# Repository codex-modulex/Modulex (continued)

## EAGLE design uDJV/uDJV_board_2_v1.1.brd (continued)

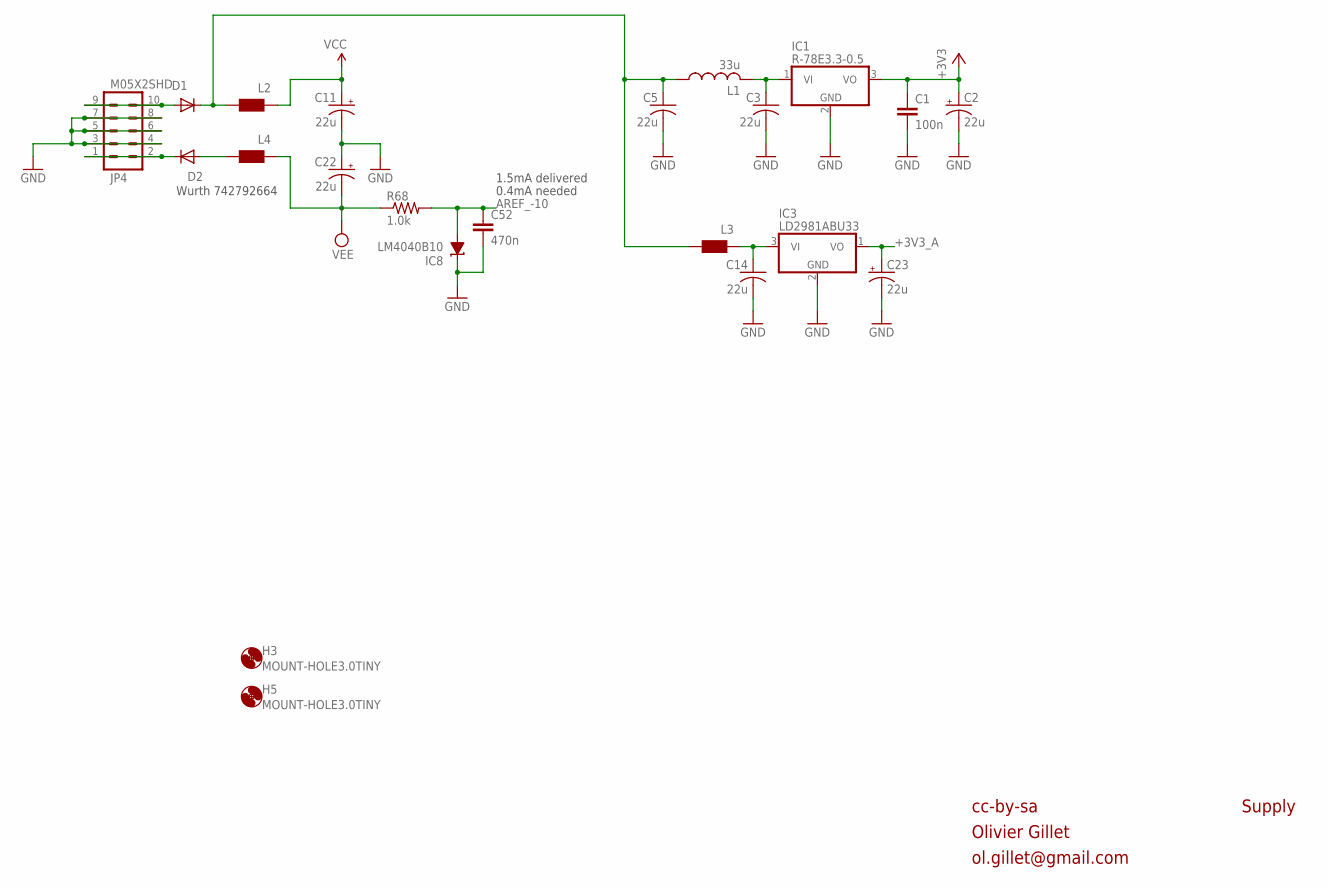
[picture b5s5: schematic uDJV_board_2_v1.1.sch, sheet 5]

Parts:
C1: 100n; PARTS_AMAN_RESISTOR_0603
C2, C11, C22, C23: 22u; PANASONIC_C
C3, C5, C14: 22u; C1206
C52: 470n; PARTS_AMAN_RESISTOR_0603
D1, D2: 1N5819HW; SOD123
H3, H5: MOUNT-HOLE3.0TINY; 3,0TINY
IC1: R-78E3.3-0.5; WE78
IC3: LD2981ABU33; SOT89
IC8: LM4040B10; DBZ_R-PDSO-G3
JP4: M05X2SHD; 2X5-SHROUDED
L1: 33u; L2012C
L2, L3, L4: WE-CBF_0603; 0603
R68: 1.0k; PARTS_AMAN_RESISTOR_0603

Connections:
+3V3: C1.1, C2.+, IC1.3 (VO); also elsewhere on the board
+3V3_A: C23.+, IC3.1 (VO); also elsewhere on the board
AREF_-10: C52.1, IC8.2 (A), R68.2; also elsewhere on the board
GND: C1.2, C2.-, C3.2, C5.2, C11.-, C14.2, C22.+, C23.-, C52.2, IC1.2 (GND), IC3.2 (GND), IC8.1 (C), JP4.3, JP4.4, JP4.5, JP4.6, JP4.7, JP4.8; also elsewhere on the board
unnamed: C14.1, IC3.3 (VI), L3.1
unnamed: C5.1, D1.C, L1.1, L2.2, L3.2
unnamed: D2.A, L4.2
unnamed: C3.1, IC1.1 (VI), L1.2
unnamed: D1.A, JP4.9, JP4.10
unnamed: D2.C, JP4.1, JP4.2
VCC: C11.+, L2.1; also elsewhere on the board
VEE: C22.-, L4.1, R68.1; also elsewhere on the board

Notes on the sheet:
0.4mA needed
cc-by-sa
Olivier Gillet
ol.gillet@gmail.com
Supply
Wurth 742792664
1.5mA delivered

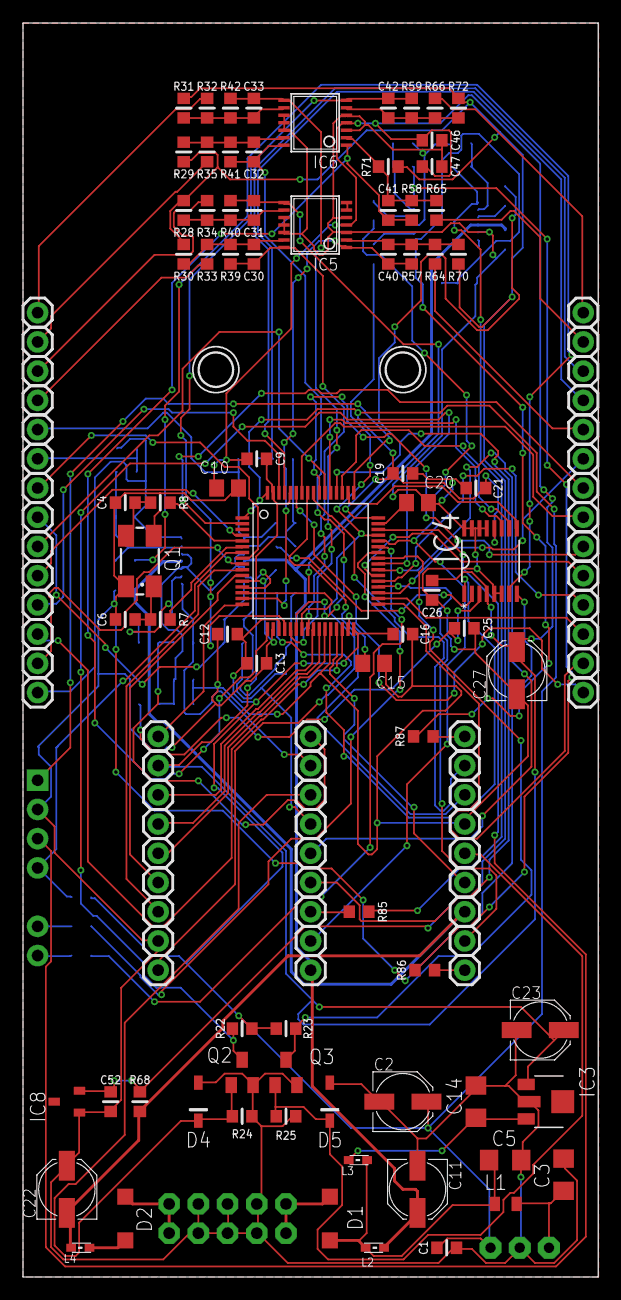
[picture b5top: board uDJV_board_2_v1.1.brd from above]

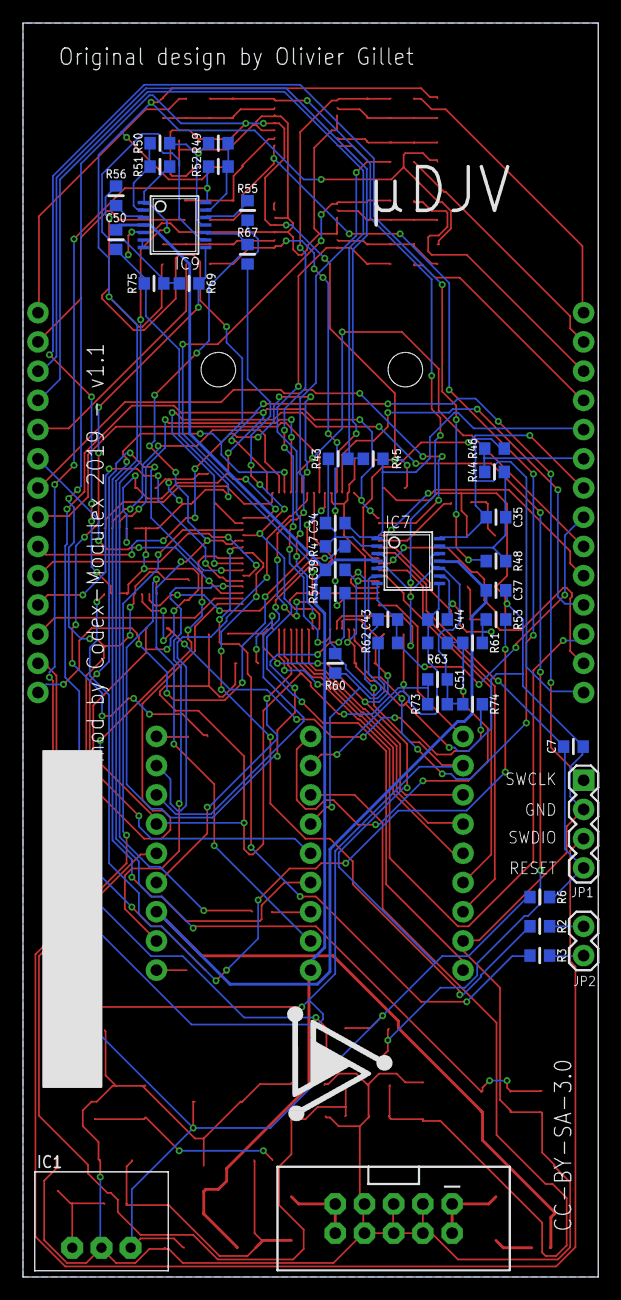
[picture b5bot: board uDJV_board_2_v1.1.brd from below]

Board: 2 copper layers, 50.0 x 109.0 mm, 178 parts (41 on the bottom side), 115 nets.

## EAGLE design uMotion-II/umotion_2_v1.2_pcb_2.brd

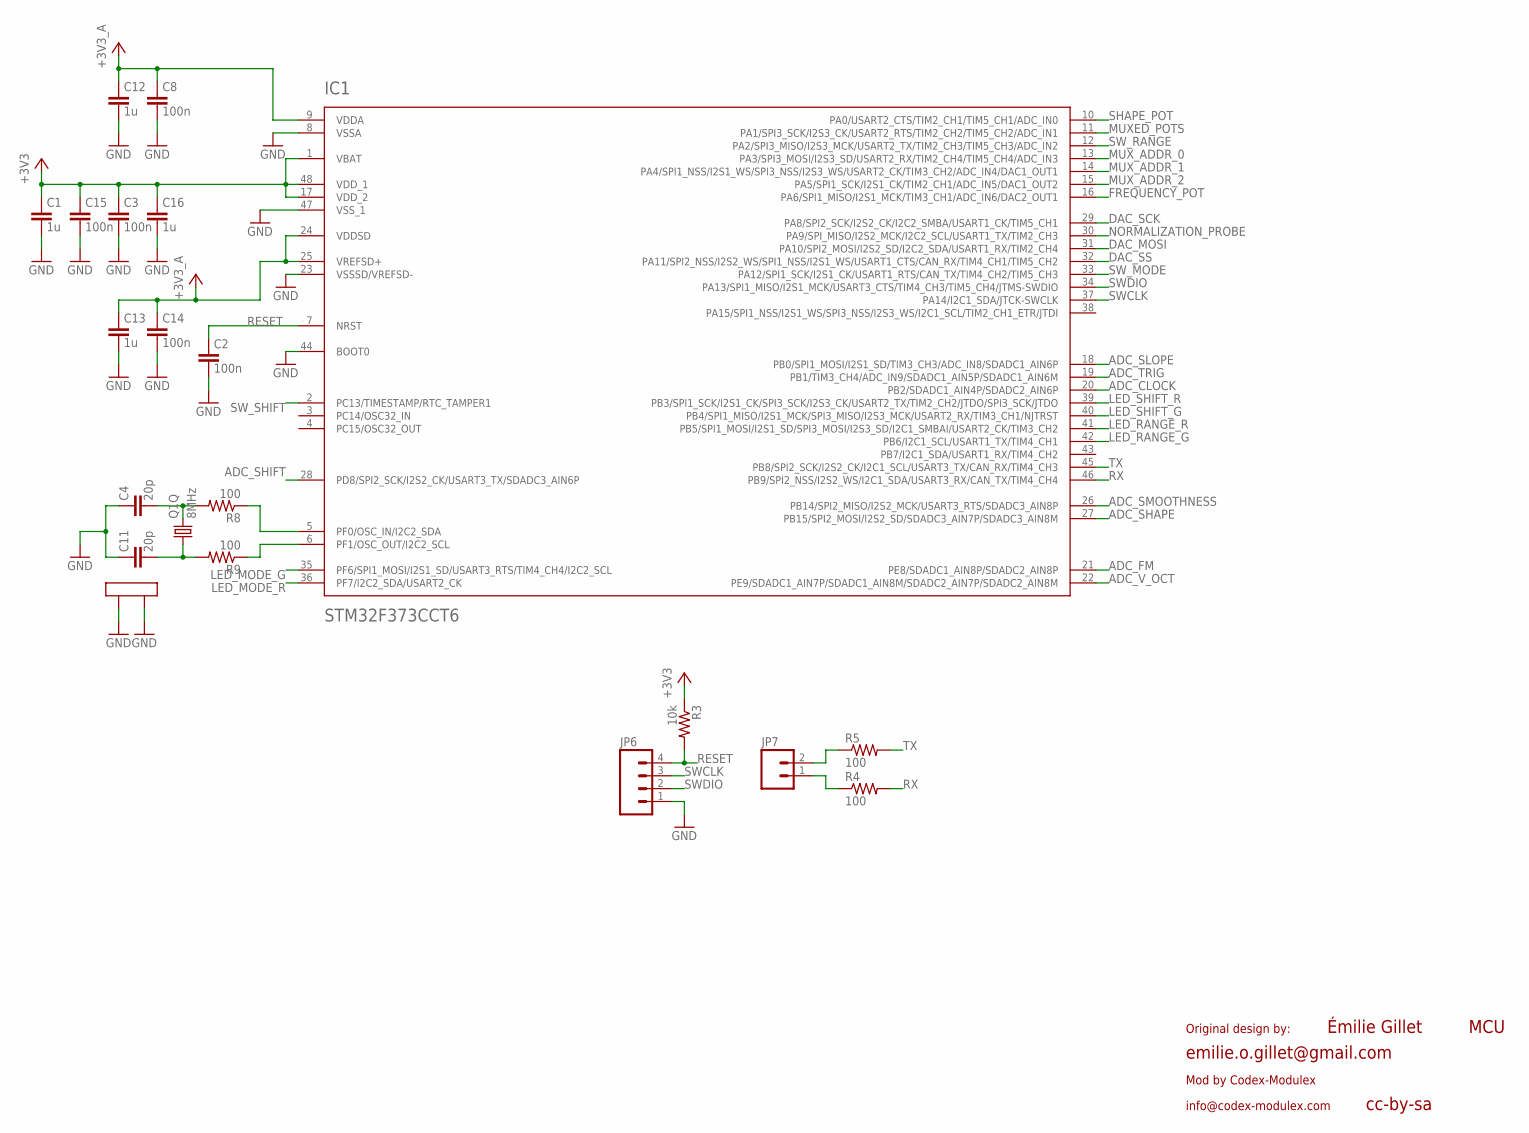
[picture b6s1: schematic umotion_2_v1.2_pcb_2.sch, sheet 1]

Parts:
C1, C12, C13, C16: 1u; PARTS_AMAN_RESISTOR_0603
C2, C3, C8, C14, C15: 100n; PARTS_AMAN_RESISTOR_0603
C4, C11: 20p; PARTS_AMAN_RESISTOR_0603
IC1: STM32F373CCT6; LQFP48
JP6: M04PTH; 1X04
JP7: M02PTH; 1X02
Q1: 8MHz; CTS406
R3: 10k; PARTS_AMAN_RESISTOR_0603
R4, R5, R8, R9: 100; PARTS_AMAN_RESISTOR_0603

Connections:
+3V3: C1.1, C3.1, C15.1, C16.1, IC1.1 (VBAT), IC1.17 (VDD_2), IC1.48 (VDD_1), R3.1; also elsewhere on the board
+3V3_A: C8.1, C12.1, C13.1, C14.1, IC1.9 (VDDA), IC1.24 (VDDSD), IC1.25 (VREFSD+); also elsewhere on the board
ADC_CLOCK: IC1.20 (PB2/SDADC1_AIN4P/SDADC2_AIN6P); also elsewhere on the board
ADC_FM: IC1.21 (PE8/SDADC1_AIN8P/SDADC2_AIN8P); also elsewhere on the board
ADC_SHAPE: IC1.27 (PB15/SPI2_MOSI/I2S2_SD/SDADC3_AIN7P/SDA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); also elsewhere on the board
ADC_SHIFT: IC1.28 (PD8/SPI2_SCK/I2S2_CK/USART3_TX/SDADC3_A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); also elsewhere on the board
ADC_SLOPE: IC1.18 (PB0/SPI1_MOSI/I2S1_SD/TIM3_CH3/ADC_IN8/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); also elsewhere on the board
ADC_SMOOTHNESS: IC1.26 (PB14/SPI2_MISO/I2S2_MCK/USART3_RTS/SDAD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); also elsewhere on the board
ADC_TRIG: IC1.19 (PB1/TIM3_CH4/ADC_IN9/SDADC1_AIN5P/SDADC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); also elsewhere on the board
ADC_V_OCT: IC1.22 (PE9/SDADC1_AIN7P/SDADC1_AIN8M/SDADC2_AI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); also elsewhere on the board
DAC_MOSI: IC1.31 (PA10/SPI2_MOSI/I2S2_SD/I2C2_SDA/USART1_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); also elsewhere on the board
DAC_SCK: IC1.29 (PA8/SPI2_SCK/I2S2_CK/I2C2_SMBA/USART1_C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); also elsewhere on the board
DAC_SS: IC1.32 (PA11/SPI2_NSS/I2S2_WS/SPI1_NSS/I2S1_WS/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); also elsewhere on the board
FREQUENCY_POT: IC1.16 (PA6/SPI1_MISO/I2S1_MCK/TIM3_CH1/ADC_IN6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); also elsewhere on the board
GND: C1.2, C2.2, C3.2, C4.1, C8.2, C11.1, C12.2, C13.2, C14.2, C15.2, C16.2, IC1.8 (VSSA), IC1.23 (VSSSD/VREFSD-), IC1.44 (BOOT0), IC1.47 (VSS_1), JP6.1, Q1.2 (LID1), Q1.4 (LID2); also elsewhere on the board
LED_MODE_G: IC1.35 (PF6/SPI1_MOSI/I2S1_SD/USART3_RTS/TIM4_C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); also elsewhere on the board
LED_MODE_R: IC1.36 (PF7/I2C2_SDA/USART2_CK); also elsewhere on the board
LED_RANGE_G: IC1.42 (PB6/I2C1_SCL/USART1_TX/TIM4_CH1); also elsewhere on the board
LED_RANGE_R: IC1.41 (PB5/SPI1_MOSI/I2S1_SD/SPI3_MOSI/I2S3_SD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); also elsewhere on the board
LED_SHIFT_G: IC1.40 (PB4/SPI1_MISO/I2S1_MCK/SPI3_MISO/I2S3_M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); also elsewhere on the board
LED_SHIFT_R: IC1.39 (PB3/SPI1_SCK/I2S1_CK/SPI3_SCK/I2S3_CK/U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); also elsewhere on the board
MUXED_POTS: IC1.11 (PA1/SPI3_SCK/I2S3_CK/USART2_RTS/TIM2_CH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); also elsewhere on the board
MUX_ADDR_0: IC1.13 (PA3/SPI3_MOSI/I2S3_SD/USART2_RX/TIM2_CH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); also elsewhere on the board
MUX_ADDR_1: IC1.14 (PA4/SPI1_NSS/I2S1_WS/SPI3_NSS/I2S3_WS/U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); also elsewhere on the board
MUX_ADDR_2: IC1.15 (PA5/SPI1_SCK/I2S1_CK/TIM2_CH1/ADC_IN5/D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); also elsewhere on the board
unnamed: IC1.5 (PF0/OSC_IN/I2C2_SDA), R8.1
unnamed: IC1.6 (PF1/OSC_OUT/I2C2_SCL), R9.1
unnamed: C4.2, Q1.3 (2), R8.2
unnamed: JP7.2, R5.1
unnamed: C11.2, Q1.1, R9.2
unnamed: JP7.1, R4.1
NORMALIZATION_PROBE: IC1.30 (PA9/SPI_MISO/I2S2_MCK/I2C2_SCL/USART1_T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); also elsewhere on the board
RESET: C2.1, IC1.7 (NRST), JP6.4, R3.2
RX: IC1.46 (PB9/SPI2_NSS/I2S2_WS/I2C1_SDA/USART3_RX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), R4.2
SHAPE_POT: IC1.10 (PA0/USART2_CTS/TIM2_CH1/TIM5_CH1/ADC_IN0); also elsewhere on the board
SWCLK: IC1.37 (PA14/I2C1_SDA/JTCK-SWCLK), JP6.3
SWDIO: IC1.34 (PA13/SPI1_MISO/I2S1_MCK/USART3_CTS/TIM4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), JP6.2
SW_MODE: IC1.33 (PA12/SPI1_SCK/I2S1_CK/USART1_RTS/CAN_TX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); also elsewhere on the board
SW_RANGE: IC1.12 (PA2/SPI3_MISO/I2S3_MCK/USART2_TX/TIM2_C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); also elsewhere on the board
SW_SHIFT: IC1.2 (PC13/TIMESTAMP/RTC_TAMPER1); also elsewhere on the board
TX: IC1.45 (PB8/SPI2_SCK/I2S2_CK/I2C1_SCL/USART3_TX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), R5.2

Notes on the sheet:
cc-by-sa
MCU
Émilie Gillet
emilie.o.gillet@gmail.com
Mod by Codex-Modulex
Original design by:
info@codex-modulex.com

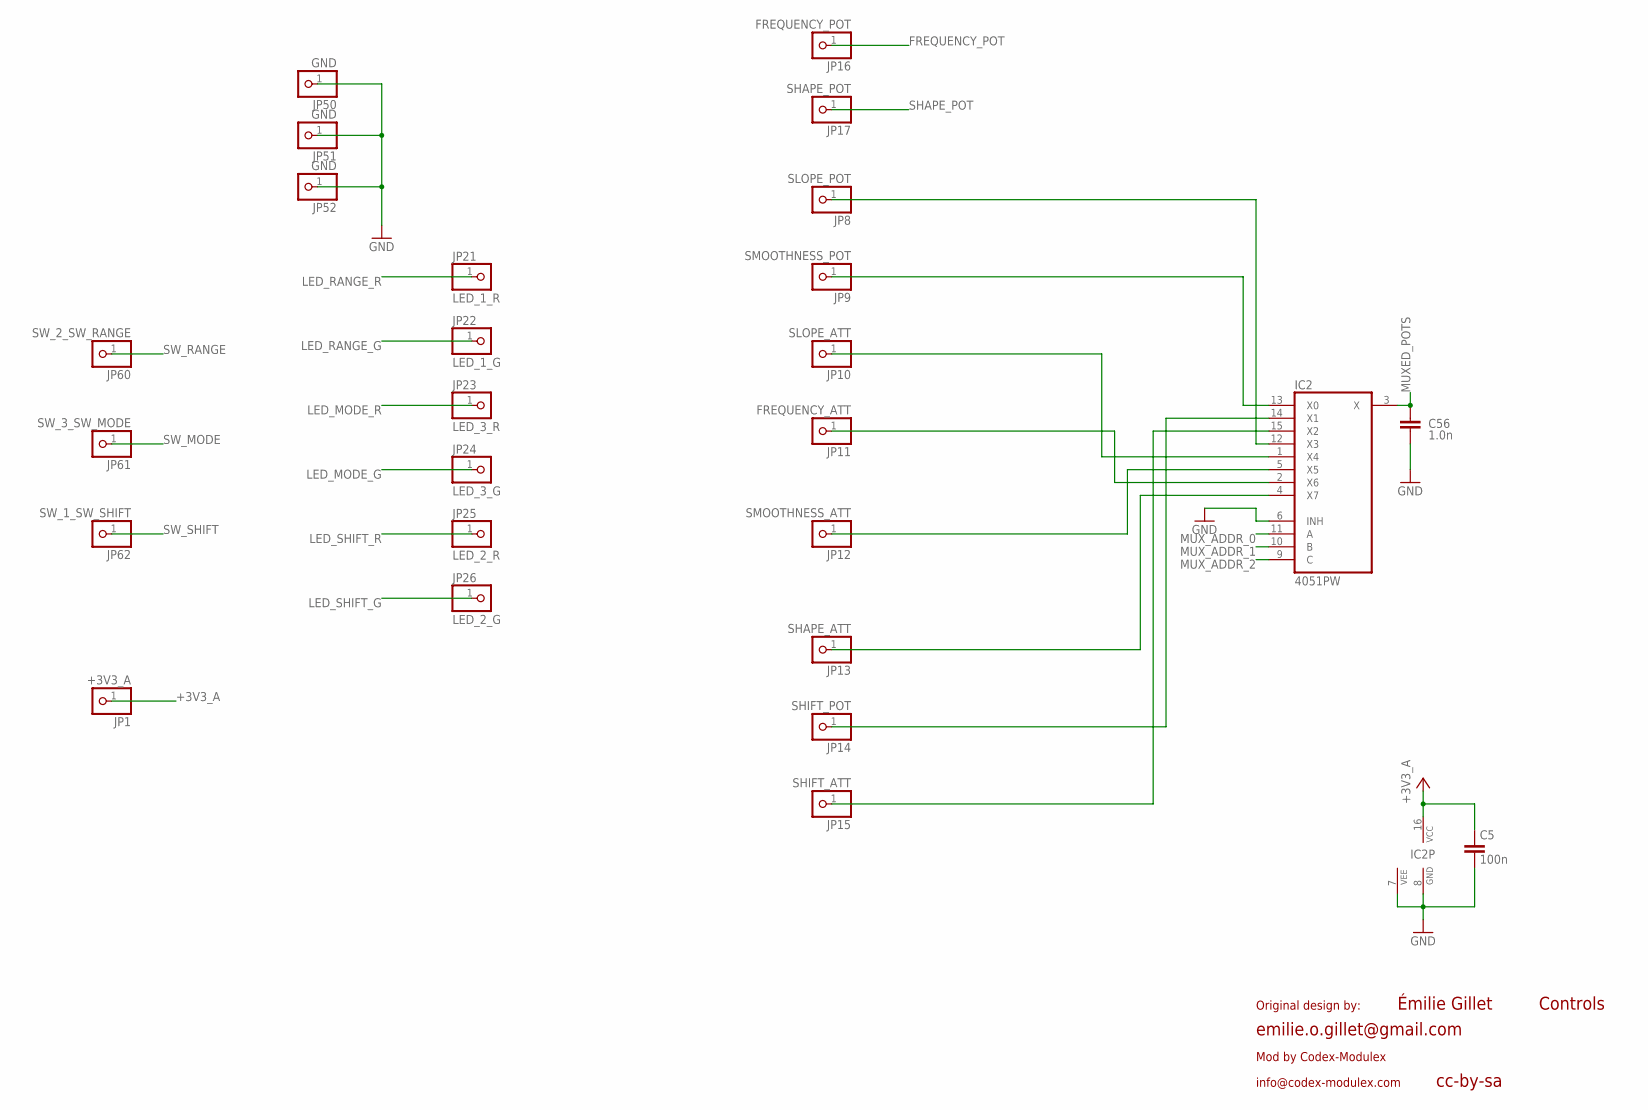
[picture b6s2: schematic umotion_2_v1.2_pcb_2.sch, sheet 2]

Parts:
C5: 100n; PARTS_AMAN_RESISTOR_0603
C56: 1.0n; PARTS_AMAN_RESISTOR_0603
IC2: 4051PW; TSSOP16_065
JP1: +3V3_A; PARTS_AMAN_1X01
JP8: SLOPE_POT; PARTS_AMAN_1X01
JP9: SMOOTHNESS_POT; PARTS_AMAN_1X01
JP10: SLOPE_ATT; PARTS_AMAN_1X01
JP11: FREQUENCY_ATT; PARTS_AMAN_1X01
JP12: SMOOTHNESS_ATT; PARTS_AMAN_1X01
JP13: SHAPE_ATT; PARTS_AMAN_1X01
JP14: SHIFT_POT; PARTS_AMAN_1X01
JP15: SHIFT_ATT; PARTS_AMAN_1X01
JP16: FREQUENCY_POT; PARTS_AMAN_1X01
JP17: SHAPE_POT; PARTS_AMAN_1X01
JP21: LED_1_R; PARTS_AMAN_1X01
JP22: LED_1_G; PARTS_AMAN_1X01
JP23: LED_3_R; PARTS_AMAN_1X01
JP24: LED_3_G; PARTS_AMAN_1X01
JP25: LED_2_R; PARTS_AMAN_1X01
JP26: LED_2_G; PARTS_AMAN_1X01
JP50, JP51, JP52: GND; PARTS_AMAN_1X01
JP60: SW_2_SW_RANGE; PARTS_AMAN_1X01
JP61: SW_3_SW_MODE; PARTS_AMAN_1X01
JP62: SW_1_SW_SHIFT; PARTS_AMAN_1X01

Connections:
+3V3_A: C5.1, IC2.16 (VCC), JP1.1; also elsewhere on the board
FREQUENCY_ATT: IC2.2 (X6), JP11.1
FREQUENCY_POT: JP16.1; also elsewhere on the board
GND: C5.2, C56.2, IC2.6 (INH), IC2.7 (VEE), IC2.8 (GND), JP50.1, JP51.1, JP52.1; also elsewhere on the board
LED_MODE_G: JP24.1; also elsewhere on the board
LED_MODE_R: JP23.1; also elsewhere on the board
LED_RANGE_G: JP22.1; also elsewhere on the board
LED_RANGE_R: JP21.1; also elsewhere on the board
LED_SHIFT_G: JP26.1; also elsewhere on the board
LED_SHIFT_R: JP25.1; also elsewhere on the board
MUXED_POTS: C56.1, IC2.3 (X); also elsewhere on the board
MUX_ADDR_0: IC2.11 (A); also elsewhere on the board
MUX_ADDR_1: IC2.10 (B); also elsewhere on the board
MUX_ADDR_2: IC2.9 (C); also elsewhere on the board
SHAPE_ATT: IC2.4 (X7), JP13.1
SHAPE_POT: JP17.1; also elsewhere on the board
SHIFT_ATT: IC2.15 (X2), JP15.1
SHIFT_POT: IC2.14 (X1), JP14.1
SLOPE_ATT: IC2.1 (X4), JP10.1
SLOPE_POT: IC2.12 (X3), JP8.1
SMOOTHNESS_ATT: IC2.5 (X5), JP12.1
SMOOTHNESS_POT: IC2.13 (X0), JP9.1
SW_MODE: JP61.1; also elsewhere on the board
SW_RANGE: JP60.1; also elsewhere on the board
SW_SHIFT: JP62.1; also elsewhere on the board

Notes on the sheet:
Controls
cc-by-sa
Émilie Gillet
emilie.o.gillet@gmail.com
Mod by Codex-Modulex
Original design by:
info@codex-modulex.com

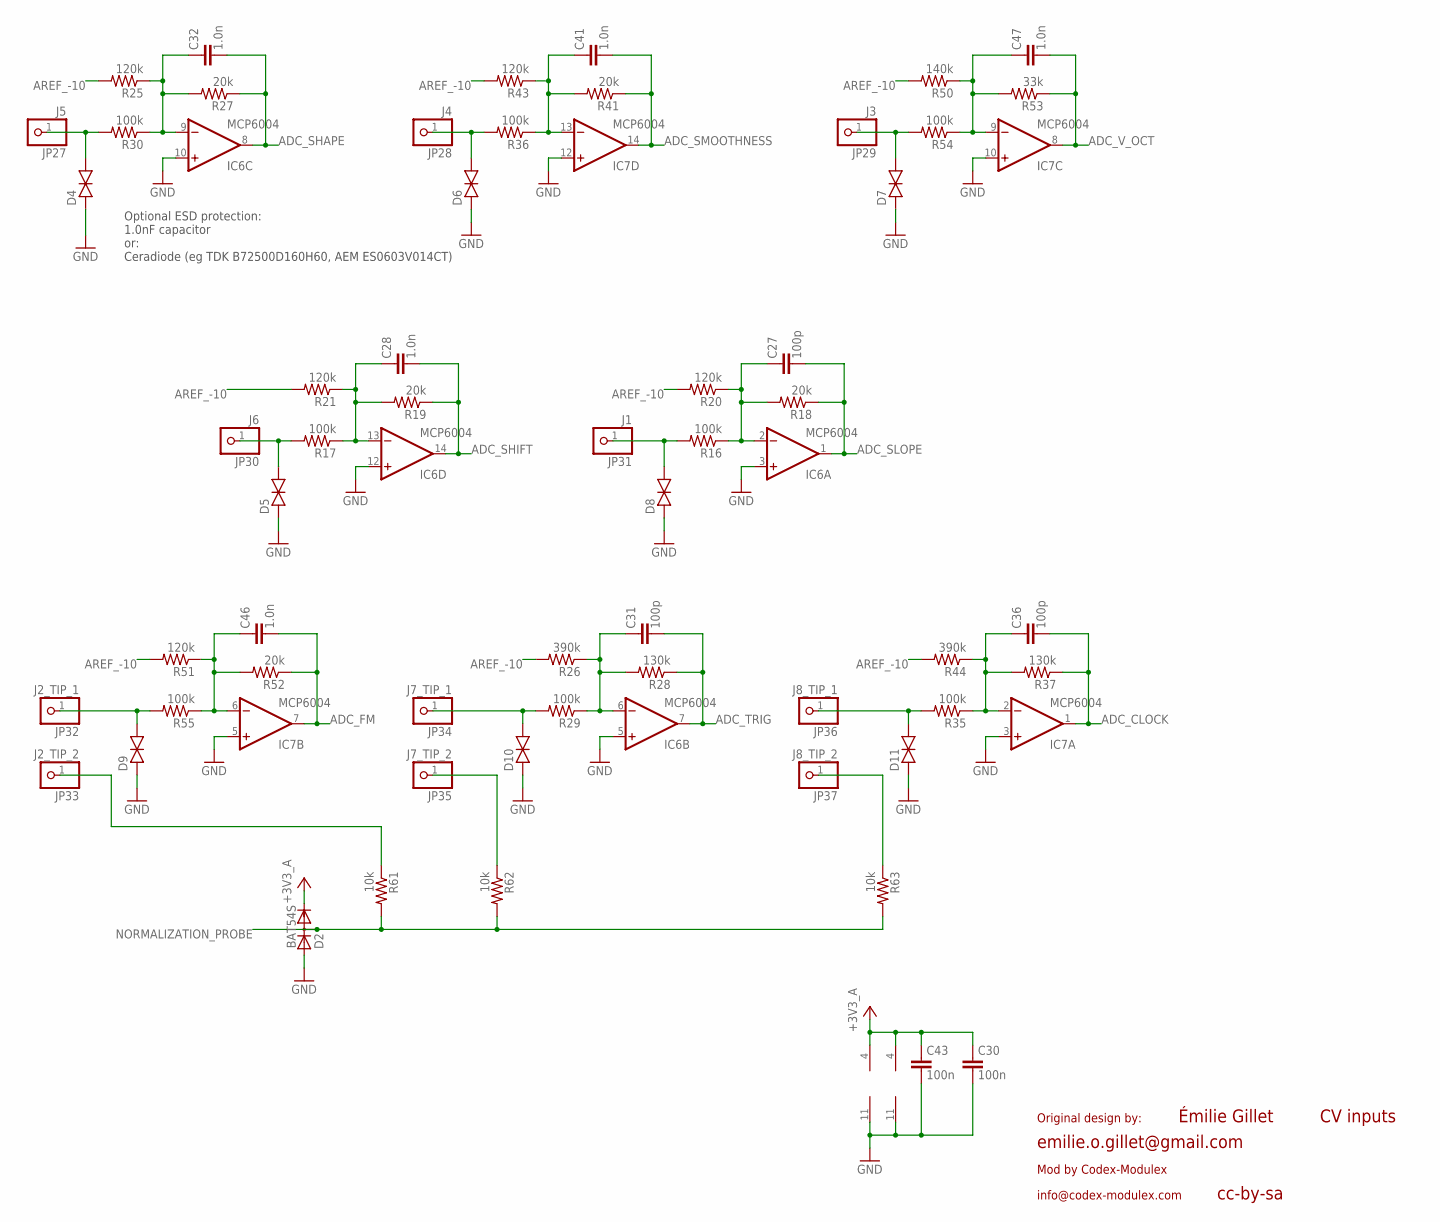
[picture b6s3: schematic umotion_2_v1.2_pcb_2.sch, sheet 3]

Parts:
C27, C31, C36: 100p; PARTS_AMAN_RESISTOR_0603
C28, C32, C41, C46, C47: 1.0n; PARTS_AMAN_RESISTOR_0603
C30, C43: 100n; PARTS_AMAN_RESISTOR_0603
D2: BAT54S; SOT23
D4, D5, D6, D7, D8, D9, D10, D11: TVS; 0603
IC6, IC7: MCP6004; TSSOP14_065
JP27: J5; PARTS_AMAN_1X01
JP28: J4; PARTS_AMAN_1X01
JP29: J3; PARTS_AMAN_1X01
JP30: J6; PARTS_AMAN_1X01
JP31: J1; PARTS_AMAN_1X01
JP32: J2_TIP_1; PARTS_AMAN_1X01
JP33: J2_TIP_2; PARTS_AMAN_1X01
JP34: J7_TIP_1; PARTS_AMAN_1X01
JP35: J7_TIP_2; PARTS_AMAN_1X01
JP36: J8_TIP_1; PARTS_AMAN_1X01
JP37: J8_TIP_2; PARTS_AMAN_1X01
R16, R17, R29, R30, R35, R36, R54, R55: 100k; PARTS_AMAN_RESISTOR_0603
R18, R19, R27, R41, R52: 20k; PARTS_AMAN_RESISTOR_0603
R20, R21, R25, R43, R51: 120k; PARTS_AMAN_RESISTOR_0603
R26, R44: 390k; PARTS_AMAN_RESISTOR_0603
R28, R37: 130k; PARTS_AMAN_RESISTOR_0603
R50: 140k; PARTS_AMAN_RESISTOR_0603
R53: 33k; PARTS_AMAN_RESISTOR_0603
R61, R62, R63: 10k; PARTS_AMAN_RESISTOR_0603

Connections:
+3V3_A: C30.1, C43.1, D2.2 (C), IC6.4 (V+), IC7.4 (V+); also elsewhere on the board
ADC_CLOCK: C36.2, IC7.1 (OUT), R37.1; also elsewhere on the board
ADC_FM: C46.2, IC7.7 (OUT), R52.1; also elsewhere on the board
ADC_SHAPE: C32.2, IC6.8 (OUT), R27.1; also elsewhere on the board
ADC_SHIFT: C28.2, IC6.14 (OUT), R19.1; also elsewhere on the board
ADC_SLOPE: C27.2, IC6.1 (OUT), R18.1; also elsewhere on the board
ADC_SMOOTHNESS: C41.2, IC7.14 (OUT), R41.1; also elsewhere on the board
ADC_TRIG: C31.2, IC6.7 (OUT), R28.1; also elsewhere on the board
ADC_V_OCT: C47.2, IC7.8 (OUT), R53.1; also elsewhere on the board
AREF_-10: R20.2, R21.2, R25.2, R26.2, R43.2, R44.2, R50.2, R51.2; also elsewhere on the board
CLOCK_IN: D11.2 (C), JP36.1, R35.2
FM_IN: D9.2 (C), JP32.1, R55.2
GND: C30.2, C43.2, D2.1 (A), D4.1 (A), D5.1 (A), D6.1 (A), D7.1 (A), D8.1 (A), D9.1 (A), D10.1 (A), D11.1 (A), IC6.3 (+IN), IC6.5 (+IN), IC6.10 (+IN), IC6.11 (V-), IC6.12 (+IN), IC7.3 (+IN), IC7.5 (+IN), IC7.10 (+IN), IC7.11 (V-), IC7.12 (+IN); also elsewhere on the board
unnamed: JP35.1, R62.1
unnamed: JP37.1, R63.1
unnamed: C27.1, IC6.2 (-IN), R16.1, R18.2, R20.1
unnamed: JP33.1, R61.1
unnamed: C28.1, IC6.13 (-IN), R17.1, R19.2, R21.1
unnamed: C47.1, IC7.9 (-IN), R50.1, R53.2, R54.1
unnamed: C46.1, IC7.6 (-IN), R51.1, R52.2, R55.1
unnamed: C31.1, IC6.6 (-IN), R26.1, R28.2, R29.1
unnamed: C32.1, IC6.9 (-IN), R25.1, R27.2, R30.1
unnamed: C36.1, IC7.2 (-IN), R35.1, R37.2, R44.1
unnamed: C41.1, IC7.13 (-IN), R36.1, R41.2, R43.1
NORMALIZATION_PROBE: D2.3 (AC), R61.2, R62.2, R63.2; also elsewhere on the board
SHAPE_IN: D4.2 (C), JP27.1, R30.2
SHIFT_IN: D5.2 (C), JP30.1, R17.2
SLOPE_IN: D8.2 (C), JP31.1, R16.2
SMOOTHNESS_IN: D6.2 (C), JP28.1, R36.2
TRIG_IN: D10.2 (C), JP34.1, R29.2
V_OCT_IN: D7.2 (C), JP29.1, R54.2

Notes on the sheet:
CV inputs
Optional ESD protection: 1.0nF capacitor or: Ceradiode (eg TDK B72500D160H60, AEM ES0603V014CT)
cc-by-sa
Émilie Gillet
emilie.o.gillet@gmail.com
Mod by Codex-Modulex
Original design by:
info@codex-modulex.com

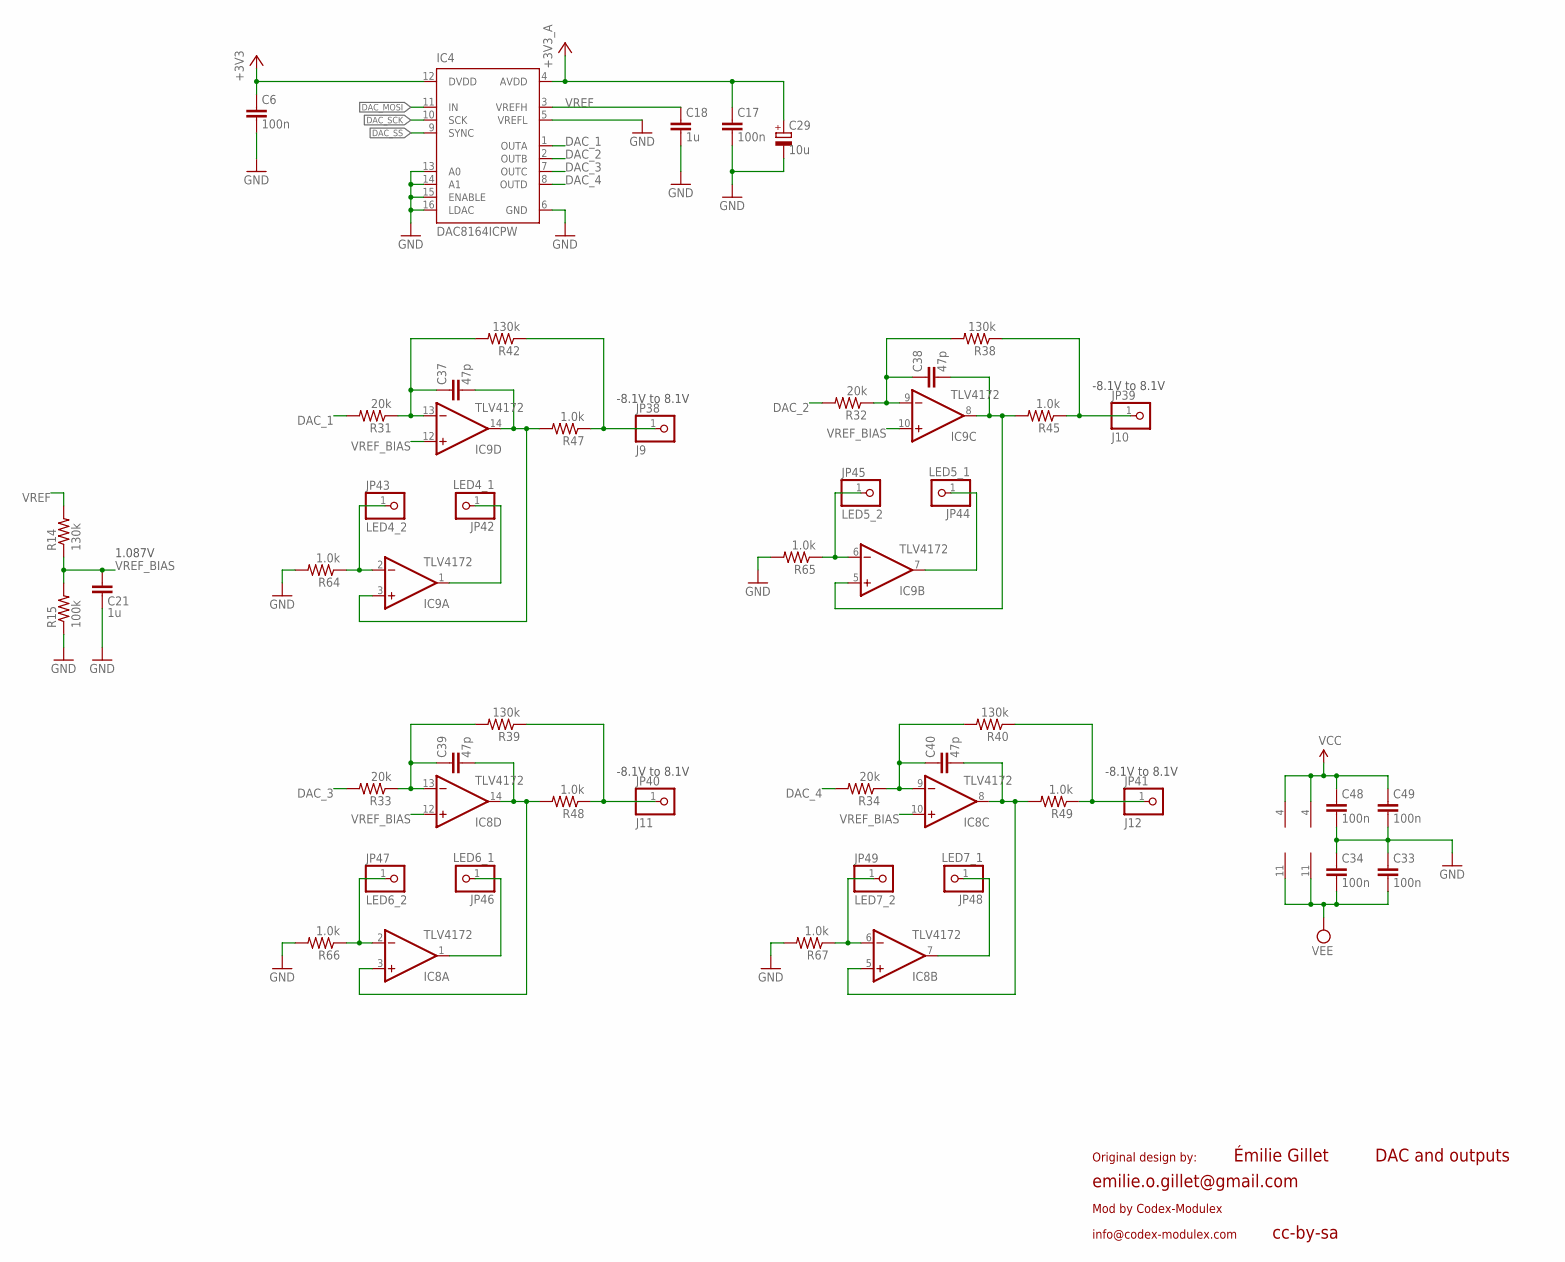
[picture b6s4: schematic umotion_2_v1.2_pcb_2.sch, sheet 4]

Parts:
C6, C17, C33, C34, C48, C49: 100n; PARTS_AMAN_RESISTOR_0603
C18, C21: 1u; PARTS_AMAN_RESISTOR_0603
C29: 10u; PANASONIC_B
C37, C38, C39, C40: 47p; PARTS_AMAN_RESISTOR_0603
IC4: DAC8164ICPW; SOP65P640X110-16N
IC8, IC9: TLV4172; TSSOP14_065
JP38: J9; PARTS_AMAN_1X01
JP39: J10; PARTS_AMAN_1X01
JP40: J11; PARTS_AMAN_1X01
JP41: J12; PARTS_AMAN_1X01
JP42: LED4_1; PARTS_AMAN_1X01
JP43: LED4_2; PARTS_AMAN_1X01
JP44: LED5_1; PARTS_AMAN_1X01
JP45: LED5_2; PARTS_AMAN_1X01
JP46: LED6_1; PARTS_AMAN_1X01
JP47: LED6_2; PARTS_AMAN_1X01
JP48: LED7_1; PARTS_AMAN_1X01
JP49: LED7_2; PARTS_AMAN_1X01
R14, R38, R39, R40, R42: 130k; PARTS_AMAN_RESISTOR_0603
R15: 100k; PARTS_AMAN_RESISTOR_0603
R31, R32, R33, R34: 20k; PARTS_AMAN_RESISTOR_0603
R45, R47, R48, R49: 1.0k; R0603
R64, R65, R66, R67: 1.0k; PARTS_AMAN_RESISTOR_0603

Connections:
+3V3: C6.1, IC4.12 (DVDD); also elsewhere on the board
+3V3_A: C17.1, C29.+, IC4.4 (AVDD); also elsewhere on the board
DAC_1: IC4.1 (OUTA), R31.2
DAC_2: IC4.2 (OUTB), R32.2
DAC_3: IC4.7 (OUTC), R33.2
DAC_4: IC4.8 (OUTD), R34.2
DAC_MOSI: IC4.11 (IN); also elsewhere on the board
DAC_SCK: IC4.10 (SCK); also elsewhere on the board
DAC_SS: IC4.9 (SYNC); also elsewhere on the board
GND: C6.2, C17.2, C18.2, C21.2, C29.-, C33.1, C34.1, C48.2, C49.2, IC4.5 (VREFL), IC4.6 (GND), IC4.13 (A0), IC4.14 (A1), IC4.15 (ENABLE), IC4.16 (LDAC), R15.1, R64.2, R65.2, R66.2, R67.2; also elsewhere on the board
unnamed: C37.2, IC9.3 (+IN), IC9.14 (OUT), R47.2
unnamed: JP40.1, R39.1, R48.1
unnamed: JP38.1, R42.1, R47.1
unnamed: C39.1, IC8.13 (-IN), R33.1, R39.2
unnamed: JP41.1, R40.1, R49.1
unnamed: C40.1, IC8.9 (-IN), R34.1, R40.2
unnamed: C38.1, IC9.9 (-IN), R32.1, R38.2
unnamed: C37.1, IC9.13 (-IN), R31.1, R42.2
unnamed: JP39.1, R38.1, R45.1
unnamed: IC9.2 (-IN), JP43.1, R64.1
unnamed: IC9.1 (OUT), JP42.1
unnamed: C38.2, IC9.5 (+IN), IC9.8 (OUT), R45.2
unnamed: IC9.6 (-IN), JP45.1, R65.1
unnamed: IC9.7 (OUT), JP44.1
unnamed: C39.2, IC8.3 (+IN), IC8.14 (OUT), R48.2
unnamed: IC8.2 (-IN), JP47.1, R66.1
unnamed: IC8.1 (OUT), JP46.1
unnamed: C40.2, IC8.5 (+IN), IC8.8 (OUT), R49.2
unnamed: IC8.6 (-IN), JP49.1, R67.1
unnamed: IC8.7 (OUT), JP48.1
VCC: C48.1, C49.1, IC8.4 (V+), IC9.4 (V+); also elsewhere on the board
VEE: C33.2, C34.2, IC8.11 (V-), IC9.11 (V-); also elsewhere on the board
VREF: C18.1, IC4.3 (VREFH), R14.2
VREF_BIAS: C21.1, IC8.10 (+IN), IC8.12 (+IN), IC9.10 (+IN), IC9.12 (+IN), R14.1, R15.2

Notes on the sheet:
DAC and outputs
-8.1V to 8.1V
1.087V
cc-by-sa
Émilie Gillet
emilie.o.gillet@gmail.com
Mod by Codex-Modulex
Original design by:
info@codex-modulex.com

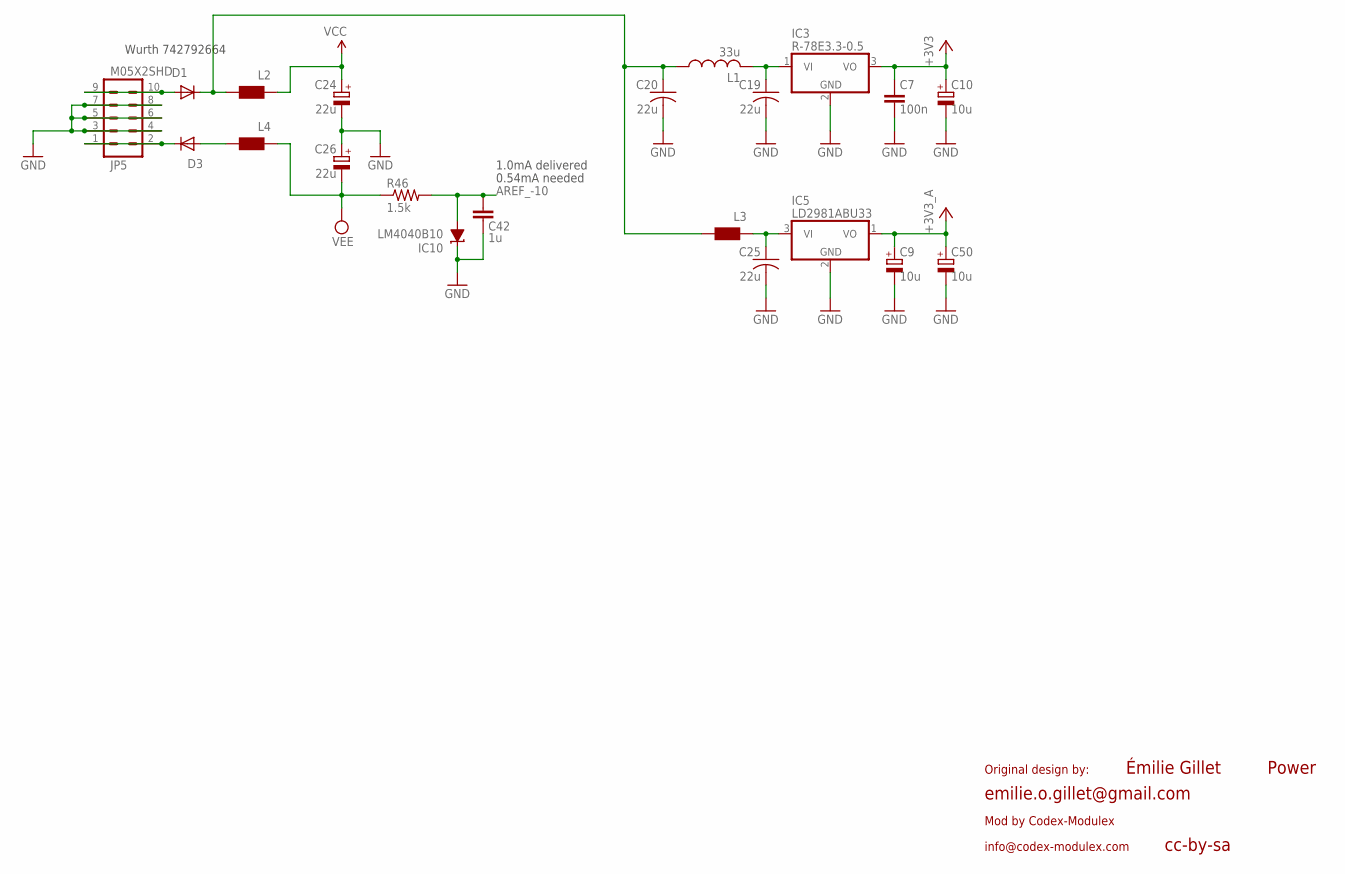
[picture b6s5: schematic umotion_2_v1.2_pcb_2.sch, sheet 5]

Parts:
C7: 100n; PARTS_AMAN_RESISTOR_0603
C9, C10, C50: 10u; PANASONIC_B
C19, C20, C25: 22u; C1206
C24, C26: 22u; PANASONIC_C
C42: 1u; PARTS_AMAN_RESISTOR_0603
D1, D3: 1N5819HW; SOD123
IC3: R-78E3.3-0.5; WE78
IC5: LD2981ABU33; SOT89
IC10: LM4040B10; DBZ_R-PDSO-G3
JP5: M05X2SHD; 2X5-SHROUDED
L1: 33u; L2012C
L2, L3, L4: WE-CBF_0603; 0603
R46: 1.5k; PARTS_AMAN_RESISTOR_0603

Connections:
+3V3: C7.1, C10.+, IC3.3 (VO); also elsewhere on the board
+3V3_A: C9.+, C50.+, IC5.1 (VO); also elsewhere on the board
AREF_-10: C42.1, IC10.2 (A), R46.2; also elsewhere on the board
GND: C7.2, C9.-, C10.-, C19.2, C20.2, C24.-, C25.2, C26.+, C42.2, C50.-, IC3.2 (GND), IC5.2 (GND), IC10.1 (C), JP5.3, JP5.4, JP5.5, JP5.6, JP5.7, JP5.8; also elsewhere on the board
unnamed: C19.1, IC3.1 (VI), L1.2
unnamed: D3.A, L4.2
unnamed: C20.1, D1.C, L1.1, L2.2, L3.2
unnamed: C25.1, IC5.3 (VI), L3.1
unnamed: D1.A, JP5.9, JP5.10
unnamed: D3.C, JP5.1, JP5.2
VCC: C24.+, L2.1; also elsewhere on the board
VEE: C26.-, L4.1, R46.1; also elsewhere on the board

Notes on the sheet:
Power
0.54mA needed
Wurth 742792664
1.0mA delivered
cc-by-sa
Émilie Gillet
emilie.o.gillet@gmail.com
Mod by Codex-Modulex
Original design by:
info@codex-modulex.com

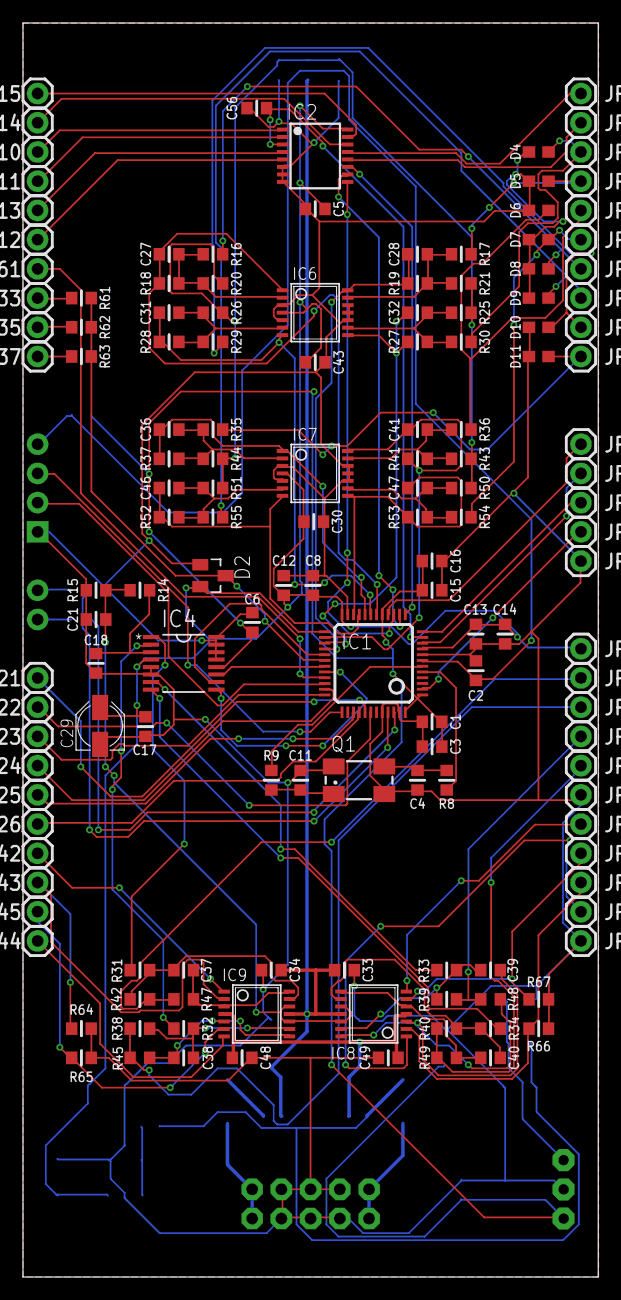
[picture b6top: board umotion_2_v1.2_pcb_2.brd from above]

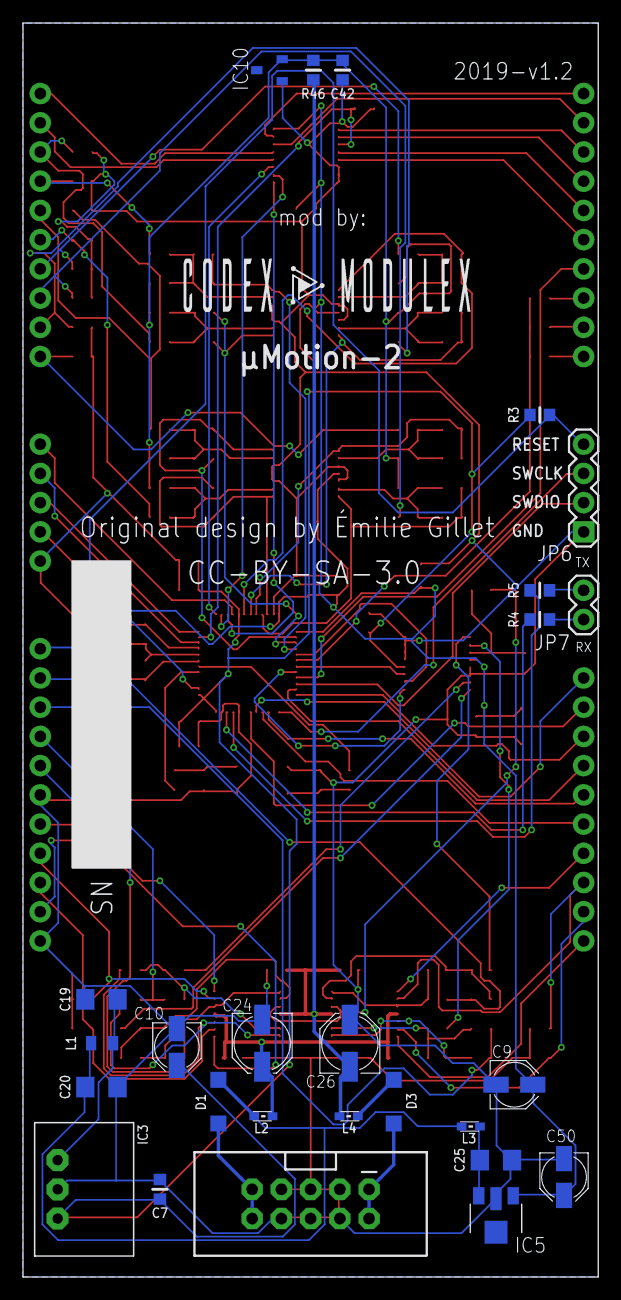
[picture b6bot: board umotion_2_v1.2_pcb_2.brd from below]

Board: 2 copper layers, 50.0 x 109.0 mm, 172 parts (26 on the bottom side), 103 nets.
